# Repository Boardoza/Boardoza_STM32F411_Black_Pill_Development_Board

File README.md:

# Boardoza STM32F411 Black Pill Development Board

The **Boardoza STM32F411CEU6 Black Pill Development Board** is a compact development board based on the **STM32F411CEU6** microcontroller, featuring a **100 MHz Arm® Cortex-M4 core** that delivers strong processing performance in a small form factor. With its balanced architecture, the board is well suited for projects that require more capability than entry-level microcontrollers.

The board includes **512 KB Flash** and **128 KB SRAM**, provides **32 general-purpose I/O pins**, and supports common interfaces such as **UART, I²C, and SPI**. Programming and debugging are supported through **USB DFU** or **SWD** using tools like **ST-Link**, and the board is compatible with **STM32CubeIDE**, **PlatformIO**, and the **Arduino STM32 framework**, allowing flexible development workflows.

## [Click here to purchase!](https://www.ozdisan.com/ureticiler/boardoza)
| Front Side | Back Side |
| :---: | :---: |
|  |  |

---

## Key Features

- **Arm® Cortex-M4 Core:** 32-bit Cortex-M4 processor running at up to 100 MHz, delivering strong performance for embedded applications.
- **Large On-Chip Memory:** Equipped with 512 KB Flash and 128 KB SRAM for complex and memory-intensive projects.
- **Rich Communication Interfaces:** Supports multiple interfaces including UART, I²C, SPI, and I²S.
- **Flexible Power Options:** Can be powered via USB Type-C or through 3.3V / 5V header pins.
- **Advanced Timers and PWM Support:** Suitable for motor control, LED driving, and precise timing applications.
- **Easy Programming and Debugging:** Supports USB DFU and SWD (ST-Link) programming and debugging.
- **Wide Software Compatibility:** Works with STM32CubeIDE, PlatformIO, and Arduino STM32 framework.

---

## Technical Specifications

**Model:** STM32F411CEU6  
**Manufacturer:** Boardoza    
**Manufacturer IC:** STMicroelectronics  
**Operating Voltage:** 3.3 V - 5 V (USB or external supply)  
**Voltage Input Type:** USB Type-C / 2.54 mm pin header  
**Core:** Arm® Cortex-M4 (32-bit with FPU)  
**Maximum Clock Frequency:** 100 MHz  
**Flash Memory:** 512 KB  
**SRAM:** 128 KB  
**GPIO Pins:** 32  
**Analog Inputs:** 10 (12-bit ADC)  
**Interfaces:** UART, SPI, I²C, I²S  
**Debug Interface:** SWD  
**Operating Temperature:** -40 °C to +85 °C  
**Board Dimensions:** 20.78 mm × 52.81 mm

---

## Board Pinout/User Guide

 > Pin functions are multiplexed. For detailed pin descriptions, alternate-function mappings, and usage examples, please refer to the Board User Guide: [STM32F411_Blackpill.pdf](./assets/STM32F411CEU6_Blackpill.pdf).

---

## Board Dimensions

---

## Step Files

[Boardoza STM32F411CEU6.step](./assets/STM32F411CEU6%20Step.step)

---

## Datasheet

[STM32F411CEU6 Datasheet.pdf](./assets/STM32F411CEU6%20Datasheet.pdf)

---

## Version History

- **V1.0.0** – Initial Release

---

## Support

- For questions or support, please contact **support@boardoza.com**

---

## **License**
### **Hardware Design**

[![CC BY-SA 4.0][cc-by-sa-shield]][cc-by-sa]

All hardware design files are licensed under [Creative Commons Attribution-ShareAlike 4.0 International License][cc-by-sa].

[cc-by-sa]: http://creativecommons.org/licenses/by-sa/4.0/
[cc-by-sa-shield]: https://img.shields.io/badge/License-CC%20BY--SA%204.0-lightgrey.svg

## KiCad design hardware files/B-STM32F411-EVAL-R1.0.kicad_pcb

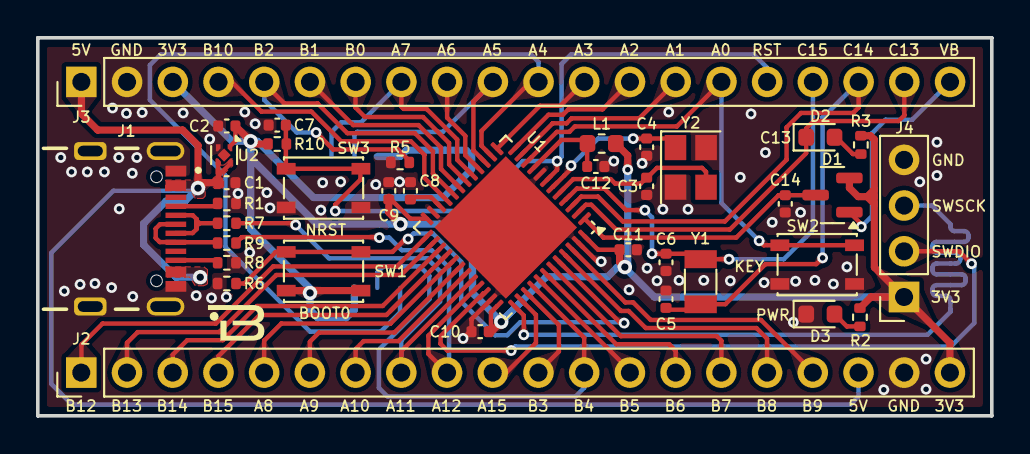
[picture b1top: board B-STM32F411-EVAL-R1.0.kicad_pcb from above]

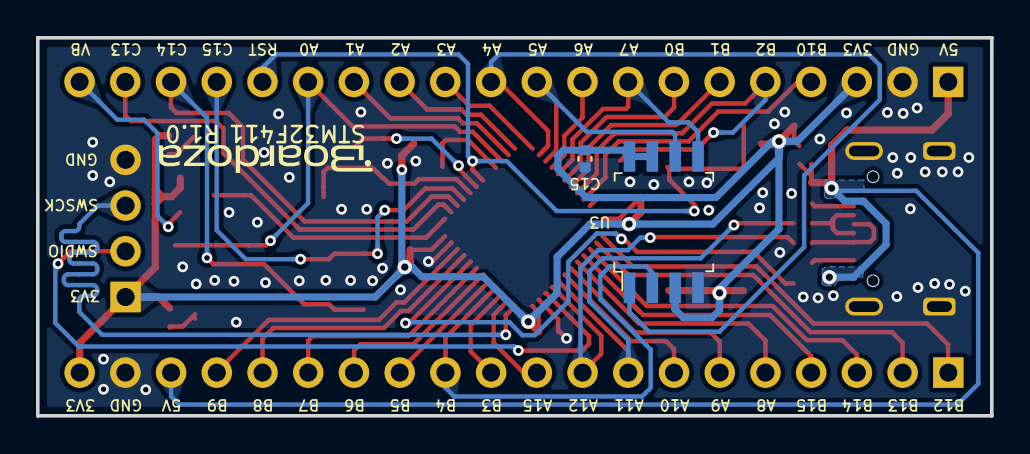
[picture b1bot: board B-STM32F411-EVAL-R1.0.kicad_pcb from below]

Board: 2 copper layers, 53.0 x 21.0 mm, 39 parts (2 on the bottom side), 51 nets.

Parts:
C1, C2: 1uF; C_0402_1005Metric
C3, C4: 10pF; C_0402_1005Metric
C5, C6: 12pF; C_0402_1005Metric
C7, C9, C10, C11, C12, C14, C15: 100nF; C_0402_1005Metric
C8: 2.2uF; C_0402_1005Metric
D1: BAT54C; SOT-23
D2, D3: LED; LED_0603_1608Metric
J1: USB_C_Receptacle_USB2.0_16P; GCT_USB4105GFA120
J2, J3: Conn_01x20; PinHeader_1x20_P2.54mm_Vertical
J4: Conn_01x04; PinSocket_1x04_P2.54mm_Vertical
L1: 10uH; L_0603_1608Metric
R1, R8: 5.1K; R_0402_1005Metric
R2, R3: 330R; R_0402_1005Metric
R5, R6, R10: 10K; R_0402_1005Metric
R7, R9: 10R; R_0402_1005Metric
SW1, SW2, SW3: SW_MEC_5E; SW_SPST_PTS810
U1: STM32F411CEU6; QFN-48-1EP_7x7mm_P0.5mm_EP5.6x5.6mm
U2: AP7343D-33FS4-7B; OnSemi_XDFN4-1EP_1.0x1.0mm_EP0.52x0.52mm
U3: W25Q32JVSSIQ-TR; SOIC-8_W5.6mm
Y1: 32.768kHz; Crystal_SMD_3215-2Pin_3.2x1.5mm
Y2: 25MHz; Crystal_SMD_3225-4Pin_3.2x2.5mm

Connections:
/BOOT0: R6.1, SW1.1, SW1.2, U1.44 (BOOT0)
/NRST: C7.1, J3.16, R10.2, SW3.1, SW3.2, U1.7 (NRST)
/PA0: J3.15, SW2.1, SW2.2, U1.10 (PA0)
/PA1: J3.14, U1.11 (PA1)
/PA2: J3.13, U1.12 (PA2)
/PA3: J3.12, U1.13 (PA3)
/PA4: J3.11, U1.14 (PA4), U3.1 (~CS)
/PA5: J3.10, U1.15 (PA5), U3.6 (CLK)
/PA6: J3.9, U1.16 (PA6)
/PA7: J3.8, U1.17 (PA7), U3.5 (DI)
/PA8: J2.5, U1.29 (PA8)
/PA9: J2.6, U1.30 (PA9)
/PA10: J2.7, U1.31 (PA10)
/PA11: J2.8, R7.2, U1.32 (PA11)
/PA12: J2.9, R9.2, U1.33 (PA12)
/PA13: J4.2, U1.34 (PA13)
/PA14: J4.3, U1.37 (PA14)
/PA15: J2.10, U1.38 (PA15)
/PB0: J3.7, U1.18 (PB0)
/PB1: J3.6, U1.19 (PB1)
/PB2: J3.5, R5.1, U1.20 (PB2)
/PB3: J2.11, U1.39 (PB3)
/PB4: J2.12, U1.40 (PB4), U3.2 (DO)
/PB5: J2.13, U1.41 (PB5)
/PB6: J2.14, U1.42 (PB6)
/PB7: J2.15, U1.43 (PB7)
/PB8: J2.16, U1.45 (PB8)
/PB9: J2.17, U1.46 (PB9)
/PB10: J3.4, U1.21 (PB10)
/PB12: J2.1, U1.25 (PB12)
/PB13: J2.2, U1.26 (PB13)
/PB14: J2.3, U1.27 (PB14)
/PB15: J2.4, U1.28 (PB15)
/PC13: D2.1 (K), J3.19, U1.2 (PC13)
/PC14: C5.1, J3.18, U1.3 (PC14), Y1.2
/PC15: C6.1, J3.17, U1.4 (PC15), Y1.1
/VB: D1.1, J3.20
/VBAT: C14.1, D1.3, U1.1 (VBAT)
/VBUS: C1.1, J1.A4_B9 (VBUS), J1.B4_A9 (VBUS), J2.18, J3.1, U2.3 (EN), U2.4 (IN)
/VDD: C2.1, C9.1, C10.1, C11.1, C15.1, D1.2, J2.20, J3.3, J4.1, L1.2, R2.1, R3.1, R10.1, SW1.3 (K), SW1.4 (A), U1.24 (VDD), U1.36 (VDD), U1.48 (VDD), U2.1 (OUT), U3.3 (~WP), U3.7 (~RST), U3.8 (VCC)
GND: C1.2, C2.2, C3.2, C4.2, C5.2, C6.2, C7.2, C8.2, C9.2, C10.2, C11.2, C12.2, C14.2, C15.2, D3.1 (K), J1.A1_B12 (GND), J1.B1_A12 (GND), J1.SH1 (SHIELD), J2.19, J3.2, J4.4, R1.2, R5.2, R6.2, R8.2, SW2.3 (K), SW2.4 (A), SW3.3 (K), SW3.4 (A), U1.8 (VSSA), U1.23 (VSS), U1.35 (VSS), U1.47 (VSS), U1.49 (VSS), U2.2 (GND), U2.5 (GND), U3.4 (GND), Y2.2, Y2.4
unnamed: D2.2 (A), R3.2
unnamed: D3.2 (A), R2.2
unnamed: J1.A5 (CC1), R1.1
unnamed: J1.B5 (CC2), R8.1
unnamed: J1.A6 (D+), J1.B6 (D+), R9.1
unnamed: J1.A7 (D-), J1.B7 (D-), R7.1
unnamed: C3.1, U1.5 (PH0), Y2.3
unnamed: C4.1, U1.6 (PH1), Y2.1
unnamed: C8.1, U1.22 (VCAP1)
unnamed: C12.1, L1.1, U1.9 (VDDA)
